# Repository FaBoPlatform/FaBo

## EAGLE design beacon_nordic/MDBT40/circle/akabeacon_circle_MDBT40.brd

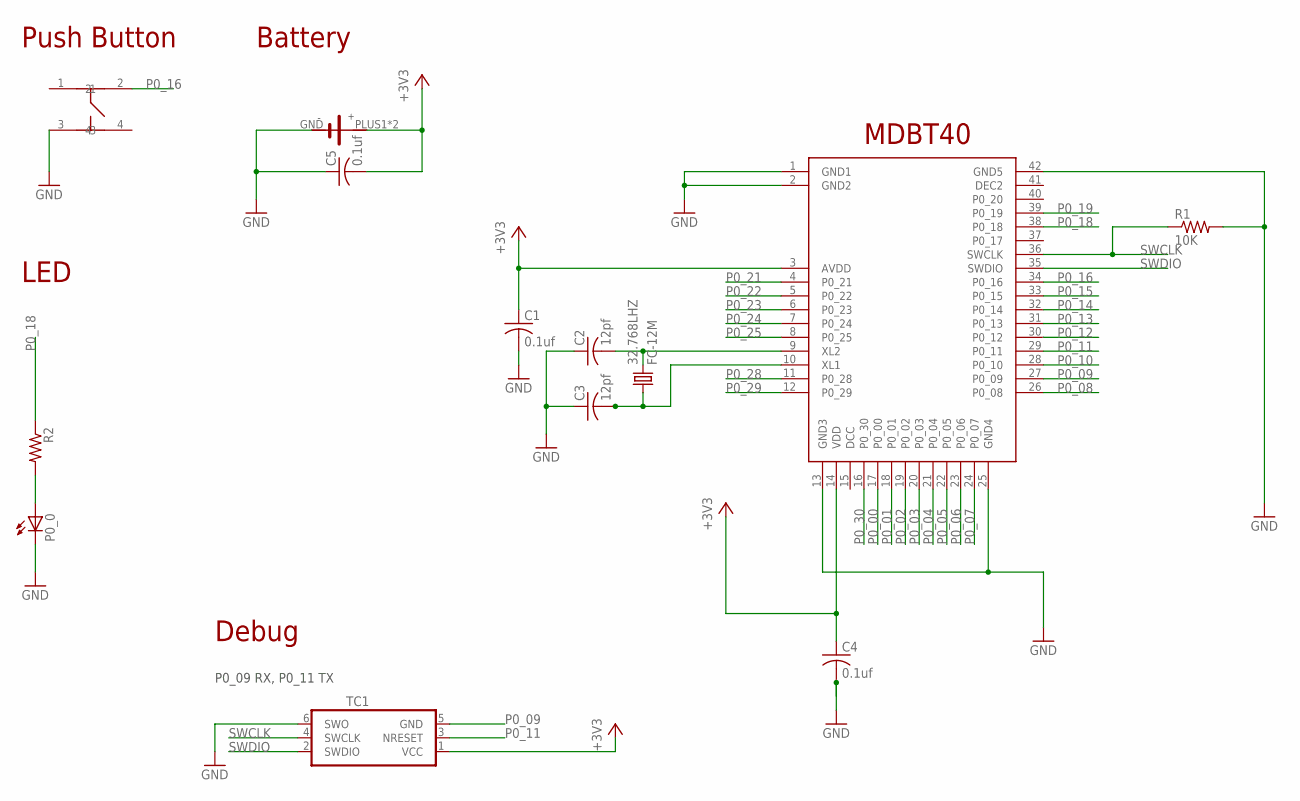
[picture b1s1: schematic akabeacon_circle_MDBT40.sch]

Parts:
32.768LHZ: FC-12M
C1, C4, C5: 0.1uf; C0603
C2, C3: 12pf; C0603
P0_0: LEDCHIP-LED0603; CHIP-LED0603
R1: 10K; R0603
R2: R-US_R0603; R0603
TC1: TC2030-IDC-NL
U$1: RAYTAC-MDBT40
U$5: SWICTH-4P(KMR2); SWITCH-4P(KMR2)
U$7: CIRCLE-TYPE1; CIRCLE-TYE1-TC2030

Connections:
+3V3: C1.1, C4.1, C5.2, TC1.1 (VCC), U$1.3 (AVDD), U$1.14 (VDD), U$7.PLUS1 (VCC), U$7.PLUS2 (VCC)
GND: C1.2, C2.1, C3.1, C4.2, C5.1, P0_0.C, R1.2, TC1.6 (SWO), U$1.1 (GND1), U$1.2 (GND2), U$1.13 (GND3), U$1.25 (GND4), U$1.42 (GND5), U$5.3, U$7.GND
unnamed: P0_0.A, R2.2
unnamed: 32.768LHZ.2, C2.2, U$1.9 (XL2)
unnamed: 32.768LHZ.1, C3.2, U$1.10 (XL1)
P0_00: U$1.17 (P0_00)
P0_01: U$1.18 (P0_01)
P0_02: U$1.19 (P0_02)
P0_03: U$1.20 (P0_03)
P0_04: U$1.21 (P0_04)
P0_05: U$1.22 (P0_05)
P0_06: U$1.23 (P0_06)
P0_07: U$1.24 (P0_07)
P0_08: U$1.26 (P0_08)
P0_09: TC1.5 (GND), U$1.27 (P0_09)
P0_10: U$1.28 (P0_10)
P0_11: TC1.3 (NRESET), U$1.29 (P0_11)
P0_12: U$1.30 (P0_12)
P0_13: U$1.31 (P0_13)
P0_14: U$1.32 (P0_14)
P0_15: U$1.33 (P0_15)
P0_16: U$1.34 (P0_16), U$5.2
P0_18: R2.1, U$1.38 (P0_18)
P0_19: U$1.39 (P0_19)
P0_21: U$1.4 (P0_21)
P0_22: U$1.5 (P0_22)
P0_23: U$1.6 (P0_23)
P0_24: U$1.7 (P0_24)
P0_25: U$1.8 (P0_25)
P0_28: U$1.11 (P0_28)
P0_29: U$1.12 (P0_29)
P0_30: U$1.16 (P0_30)
SWCLK: R1.1, TC1.4 (SWCLK), U$1.36 (SWCLK)
SWDIO: TC1.2 (SWDIO), U$1.35 (SWDIO)

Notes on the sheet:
Battery
Push Button
MDBT40
LED
Debug
P0_09 RX, P0_11 TX

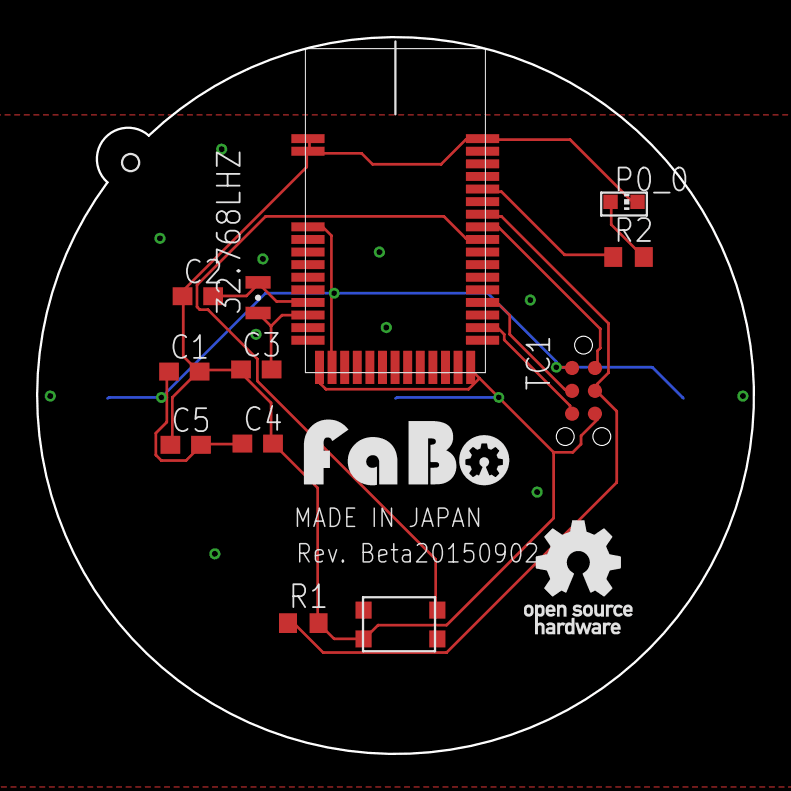
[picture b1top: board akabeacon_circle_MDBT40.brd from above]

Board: 2 copper layers, 39.8 x 39.8 mm, 15 parts (0 on the bottom side), 11 nets.

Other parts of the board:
U$2: LOGO_FABO_M
U$4: LOGO_OSHW_T_M

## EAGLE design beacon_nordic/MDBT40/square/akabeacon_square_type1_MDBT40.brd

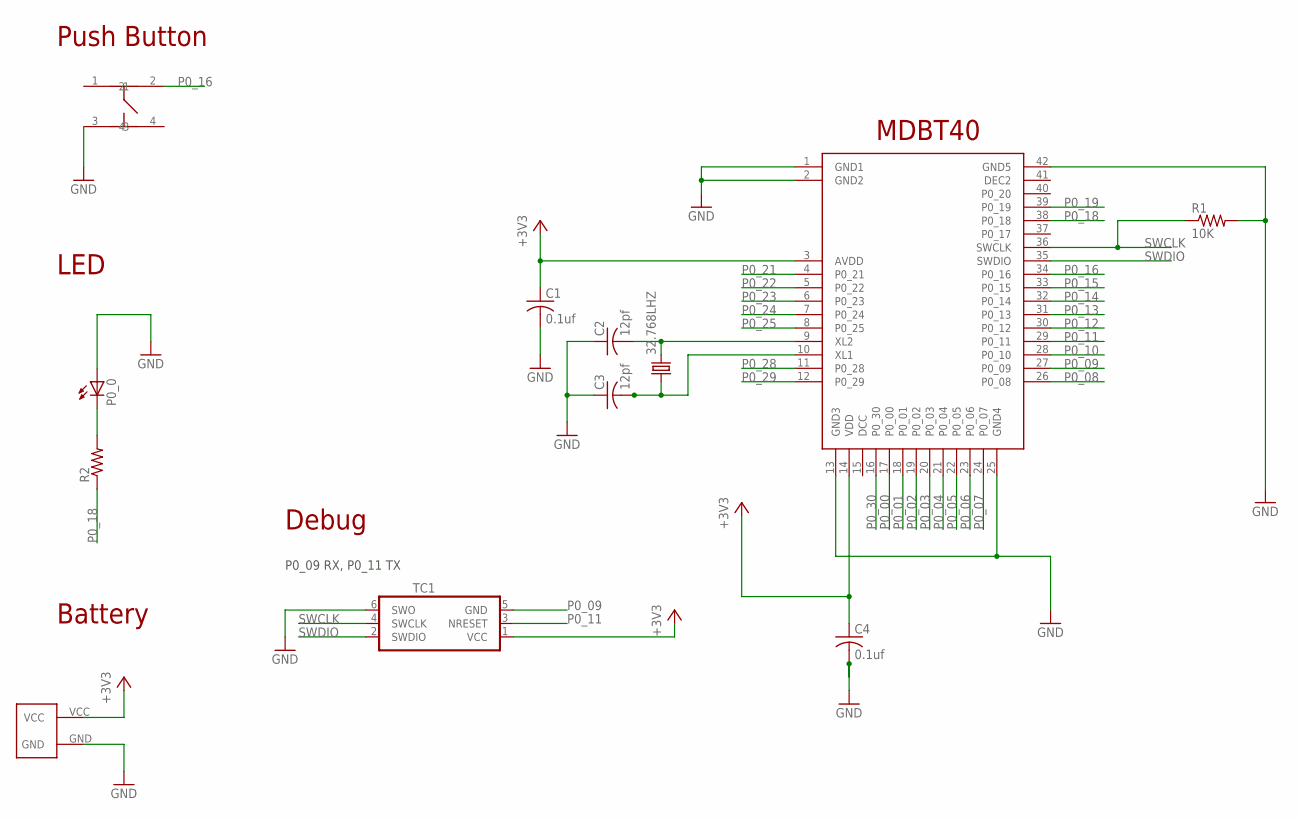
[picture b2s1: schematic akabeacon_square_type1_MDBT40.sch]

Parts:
32.768LHZ: FC-12M
C1, C4: 0.1uf; C0603
C2, C3: 12pf; C0603
P0_0: LEDCHIP-LED0603; CHIP-LED0603
R1: 10K; R0603
R2: R-US_R0603; R0603
TC1: TC2030-IDC-NL
U$2: SQUARE-TYPE1; SQUARE-TYPE1-TC2030
U$3: RAYTAC-MDBT40
U$6: SWICTH-4P(KMR2); SWITCH-4P(KMR2)

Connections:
+3V3: C1.1, C4.1, TC1.1 (VCC), U$2.VCC, U$3.3 (AVDD), U$3.14 (VDD)
GND: C1.2, C2.1, C3.1, C4.2, P0_0.A, R1.2, TC1.6 (SWO), U$2.GND, U$3.1 (GND1), U$3.2 (GND2), U$3.13 (GND3), U$3.25 (GND4), U$3.42 (GND5), U$6.3
LED1: P0_0.C, R2.2
unnamed: 32.768LHZ.2, C2.2, U$3.9 (XL2)
unnamed: 32.768LHZ.1, C3.2, U$3.10 (XL1)
P0_00: U$3.17 (P0_00)
P0_01: U$3.18 (P0_01)
P0_02: U$3.19 (P0_02)
P0_03: U$3.20 (P0_03)
P0_04: U$3.21 (P0_04)
P0_05: U$3.22 (P0_05)
P0_06: U$3.23 (P0_06)
P0_07: U$3.24 (P0_07)
P0_08: U$3.26 (P0_08)
P0_09: TC1.5 (GND), U$3.27 (P0_09)
P0_10: U$3.28 (P0_10)
P0_11: TC1.3 (NRESET), U$3.29 (P0_11)
P0_12: U$3.30 (P0_12)
P0_13: U$3.31 (P0_13)
P0_14: U$3.32 (P0_14)
P0_15: U$3.33 (P0_15)
P0_16: U$3.34 (P0_16), U$6.2
P0_18: R2.1, U$3.38 (P0_18)
P0_19: U$3.39 (P0_19)
P0_21: U$3.4 (P0_21)
P0_22: U$3.5 (P0_22)
P0_23: U$3.6 (P0_23)
P0_24: U$3.7 (P0_24)
P0_25: U$3.8 (P0_25)
P0_28: U$3.11 (P0_28)
P0_29: U$3.12 (P0_29)
P0_30: U$3.16 (P0_30)
SWCLK: R1.1, TC1.4 (SWCLK), U$3.36 (SWCLK)
SWDIO: TC1.2 (SWDIO), U$3.35 (SWDIO)

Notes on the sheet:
Battery
Push Button
Debug
MDBT40
LED
P0_09 RX, P0_11 TX

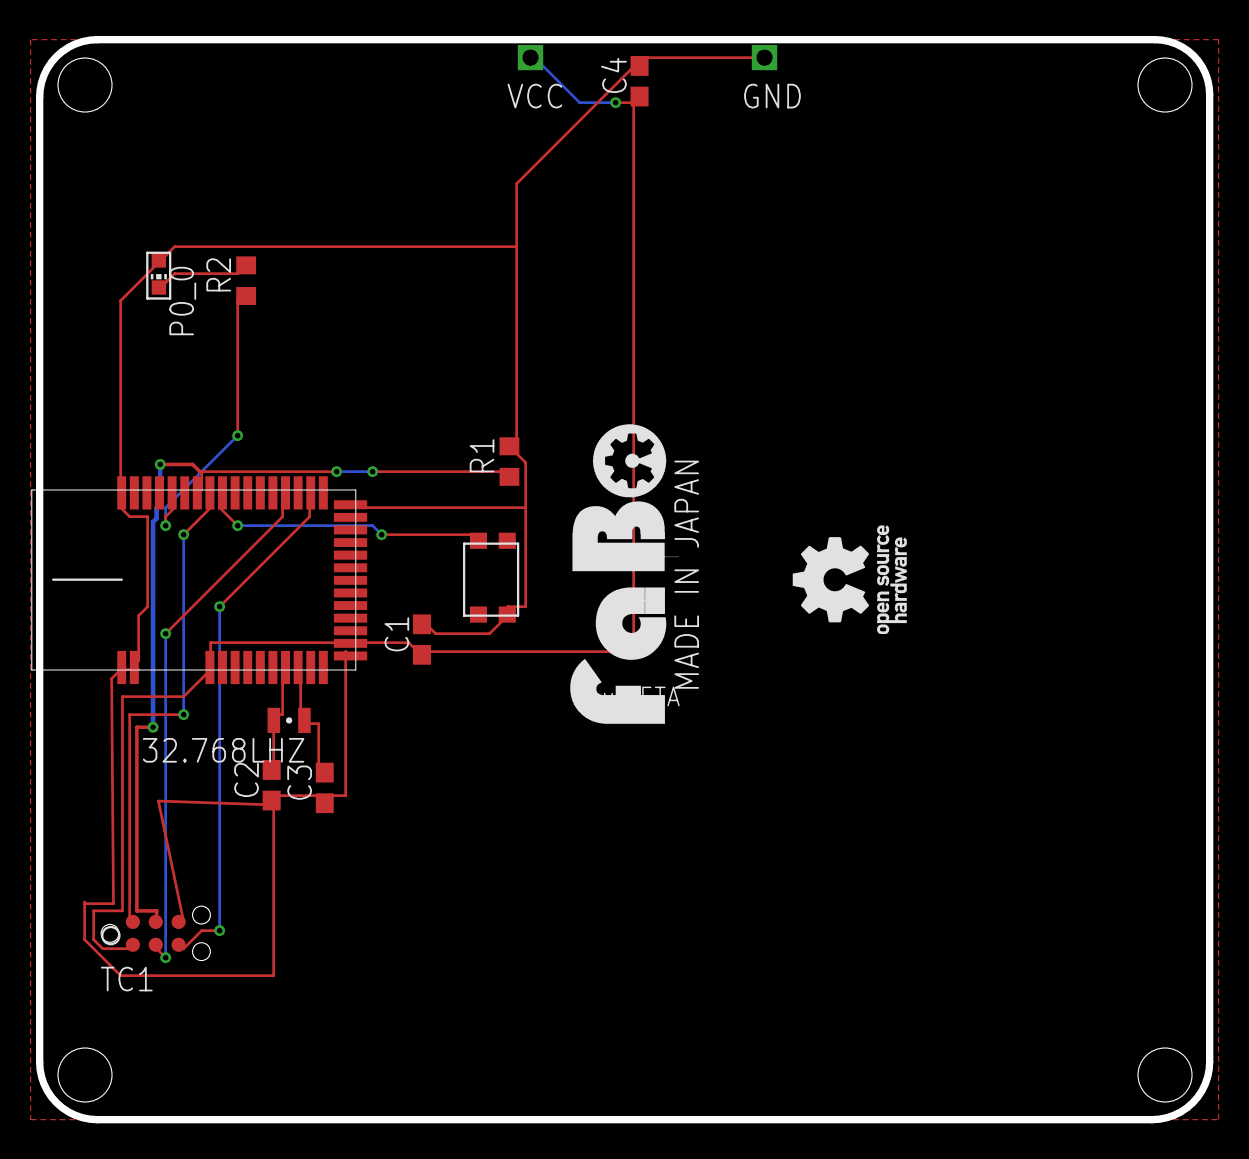
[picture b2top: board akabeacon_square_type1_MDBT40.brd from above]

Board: 2 copper layers, 65.0 x 60.0 mm, 12 parts (0 on the bottom side), 11 nets.

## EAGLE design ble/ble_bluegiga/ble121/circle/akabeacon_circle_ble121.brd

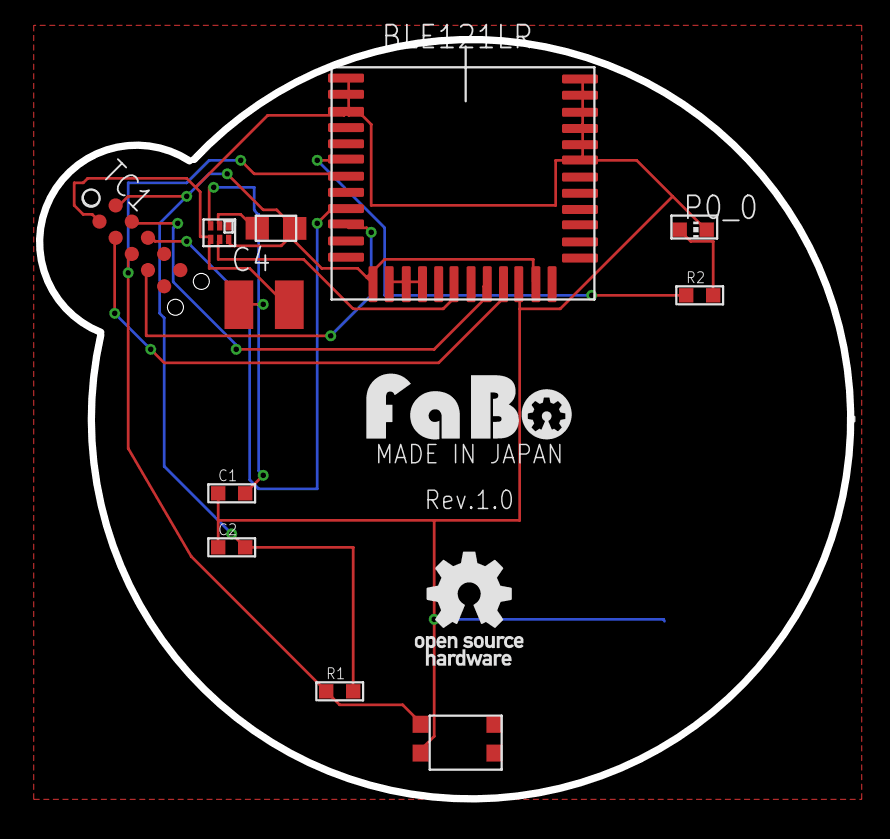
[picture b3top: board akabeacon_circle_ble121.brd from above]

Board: 2 copper layers, 14 parts (0 on the bottom side), 13 nets.

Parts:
BLE1: BLUEGIGA-BLE121LR
C1, C2: 2.2uf; 0603
C4: 100uf; C3225
INDUCTOR1: INDUCTOR-0805
P0_0: CHIP-LED0603
R1: 10k; 0603
R2: 180; 0603
TC1: TC2050-IDC; TC2050-IDC-NL
TPS1: TI-TPS62730
U$1: CIRCLE-TYPE1; CIRCLE-TYE1-TC2030
U$2: LOGO_FABO_M
U$4: LOGO_OSHW_T_M
U$5: SWICTH-4P(KMR2); SWITCH-4P(KMR2)

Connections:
3.3V: BLE1.13, BLE1.23, C2.2, INDUCTOR1.P$2, R1.2, TC1.2, TPS1.6
DEBUG_CLOCK: BLE1.20, TC1.4
DEBUG_DATA: BLE1.21, TC1.3
GND: BLE1.1, BLE1.2, BLE1.3, BLE1.22, BLE1.31, BLE1.32, BLE1.33, BLE1.34, BLE1.35, BLE1.36, C1.1, C2.1, C4.2, P0_0.C, TC1.1, TPS1.4, U$1.GND, U$5.3
unnamed: C1.2, C4.1, TPS1.3, U$1.VCC
unnamed: P0_0.A, R2.2
unnamed: INDUCTOR1.P$1, TPS1.2
unnamed: BLE1.14, BLE1.15, BLE1.16
P0_0: BLE1.6, R2.1
P0_4: BLE1.9, TC1.6
P0_5: BLE1.10, TC1.7
P1_7: BLE1.18, TPS1.5
RESET: BLE1.7, R1.1, TC1.5, U$5.1

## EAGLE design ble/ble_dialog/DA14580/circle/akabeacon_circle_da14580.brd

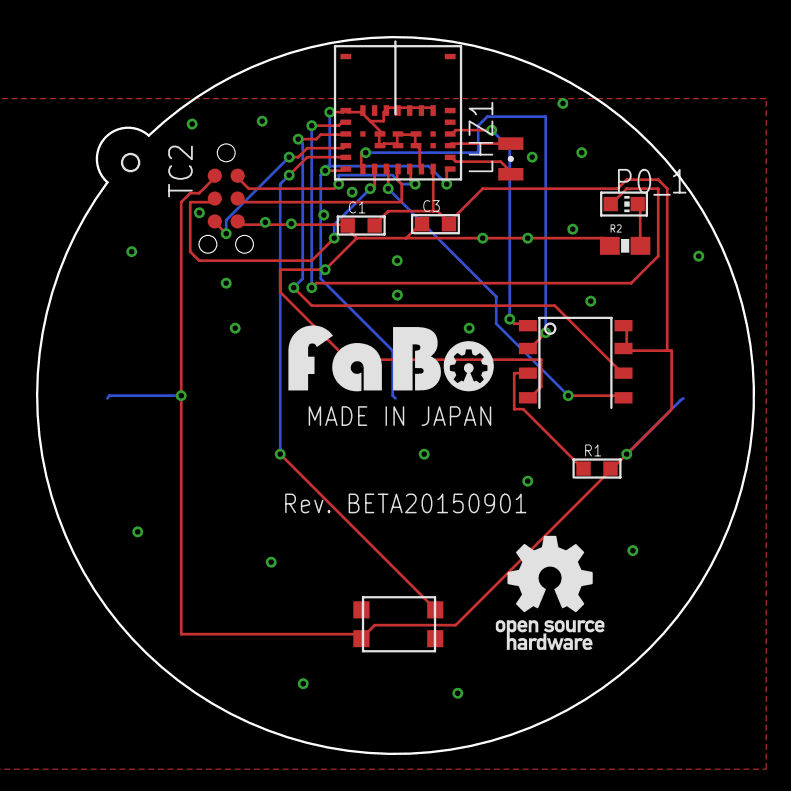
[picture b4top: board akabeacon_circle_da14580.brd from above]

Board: 2 copper layers, 39.8 x 39.8 mm, 13 parts (0 on the bottom side), 16 nets.

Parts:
C1, C3: 2.2uf; 0603
LHZ1: FC-12M
P0_1: CHIP-LED0603
R1: RESISTOR0603; 0603
R2: 180; 0603-RES
TC2: TC2030-IDC-NL
U$1: MURATA-TYPEZY; MURATA_TYPEZY
U$2: LOGO_FABO_M
U$3: CIRCLE-TYPE1; CIRCLE-TYE1-TC2030
U$5: FLASH-MEMORY-2M(WINBOND)
U$6: LOGO_OSHW_T_M
U$7: SWICTH-4P(KMR2); SWITCH-4P(KMR2)

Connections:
+3V3: C1.2, C3.2, R1.2, TC2.1, U$1.7, U$3.PLUS1, U$3.PLUS2, U$5.HOLD#, U$5.VCC, U$7.3
GND: C1.1, C3.1, R2.1, TC2.6, U$1.6, U$1.8, U$1.14, U$1.15, U$1.16, U$1.17, U$1.18, U$1.20, U$1.21, U$1.26, U$1.27, U$1.28, U$1.29, U$1.32, U$1.33, U$1.34, U$3.GND, U$5.GND
LED1: P0_1.C, R2.2
unnamed: R1.1, U$5.WP#
P0_0: U$1.23, U$5.CLK
P0_1: P0_1.A, U$1.22
P0_3: U$1.11, U$5.CS
P0_4: TC2.5, U$1.24
P0_5: U$1.1, U$5.DO
P0_6: U$1.3, U$5.DI
P0_7: TC2.3, U$1.2
RST: U$1.25, U$7.2
SWCLK: TC2.4, U$1.4
SWDIO: TC2.2, U$1.5
XTAL32KM: LHZ1.2, U$1.10
XTAL32KP: LHZ1.1, U$1.9

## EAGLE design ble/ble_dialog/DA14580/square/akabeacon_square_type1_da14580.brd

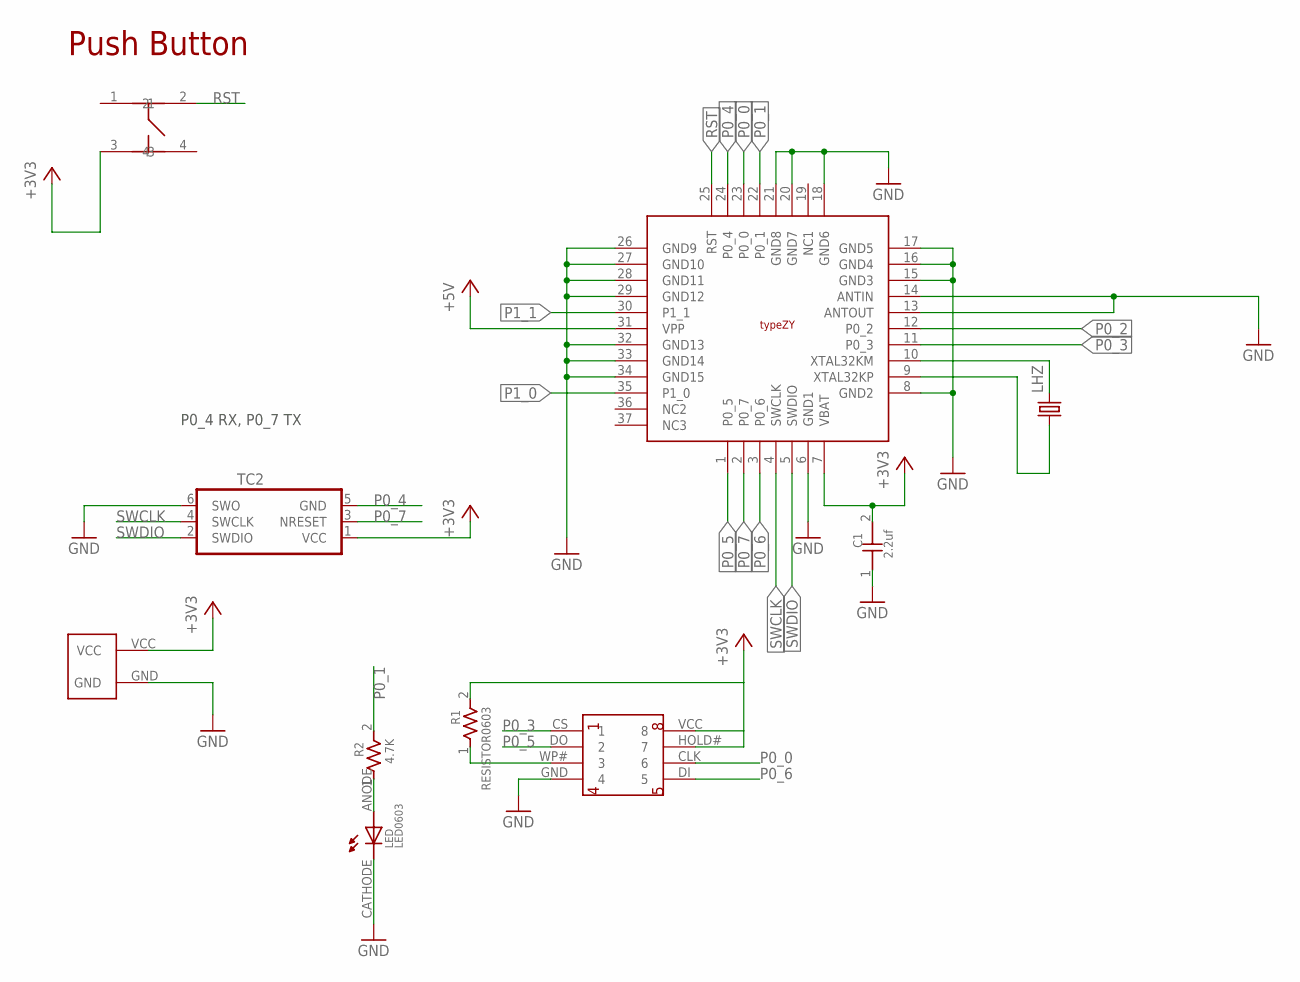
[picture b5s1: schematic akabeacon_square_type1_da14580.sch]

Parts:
C1: 2.2uf; 0603
LED: LED0603; 0603
LHZ: FC-12M
R1: RESISTOR0603; 0603
R2: 4.7K; 0603
TC2: TC2030-IDC-NL
U$2: SQUARE-TYPE1; SQUARE-TYPE1-TC2030
U$3: FLASH-MEMORY-2M(WINBOND)
U$7: SWICTH-4P(KMR2); SWITCH-4P(KMR2)
U$9: MURATA-TYPEZY; MURATA_TYPEZY

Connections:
+3V3: C1.2, R1.2, TC2.1 (VCC), U$2.VCC, U$3.HOLD# (7), U$3.VCC (8), U$7.3, U$9.7 (VBAT)
+5V: U$9.31 (VPP)
GND: C1.1, LED.CATHODE, TC2.6 (SWO), U$2.GND, U$3.GND (4), U$9.6 (GND1), U$9.8 (GND2), U$9.13 (ANTOUT), U$9.14 (ANTIN), U$9.15 (GND3), U$9.16 (GND4), U$9.17 (GND5), U$9.18 (GND6), U$9.20 (GND7), U$9.21 (GND8), U$9.26 (GND9), U$9.27 (GND10), U$9.28 (GND11), U$9.29 (GND12), U$9.32 (GND13), U$9.33 (GND14), U$9.34 (GND15)
unnamed: R1.1, U$3.WP# (3)
unnamed: LED.ANODE, R2.1
P0_0: U$3.CLK (6), U$9.23 (P0_0)
P0_1: R2.2, U$9.22 (P0_1)
P0_2: U$9.12 (P0_2)
P0_3: U$3.CS (1), U$9.11 (P0_3)
P0_4: TC2.5 (GND), U$9.24 (P0_4)
P0_5: U$3.DO (2), U$9.1 (P0_5)
P0_6: U$3.DI (5), U$9.3 (P0_6)
P0_7: TC2.3 (NRESET), U$9.2 (P0_7)
P1_0: U$9.35 (P1_0)
P1_1: U$9.30 (P1_1)
RST: U$7.2, U$9.25 (RST)
SWCLK: TC2.4 (SWCLK), U$9.4 (SWCLK)
SWDIO: TC2.2 (SWDIO), U$9.5 (SWDIO)
XTAL32KM: LHZ.2, U$9.10 (XTAL32KM)
XTAL32KP: LHZ.1, U$9.9 (XTAL32KP)

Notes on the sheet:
Push Button
P0_4 RX, P0_7 TX

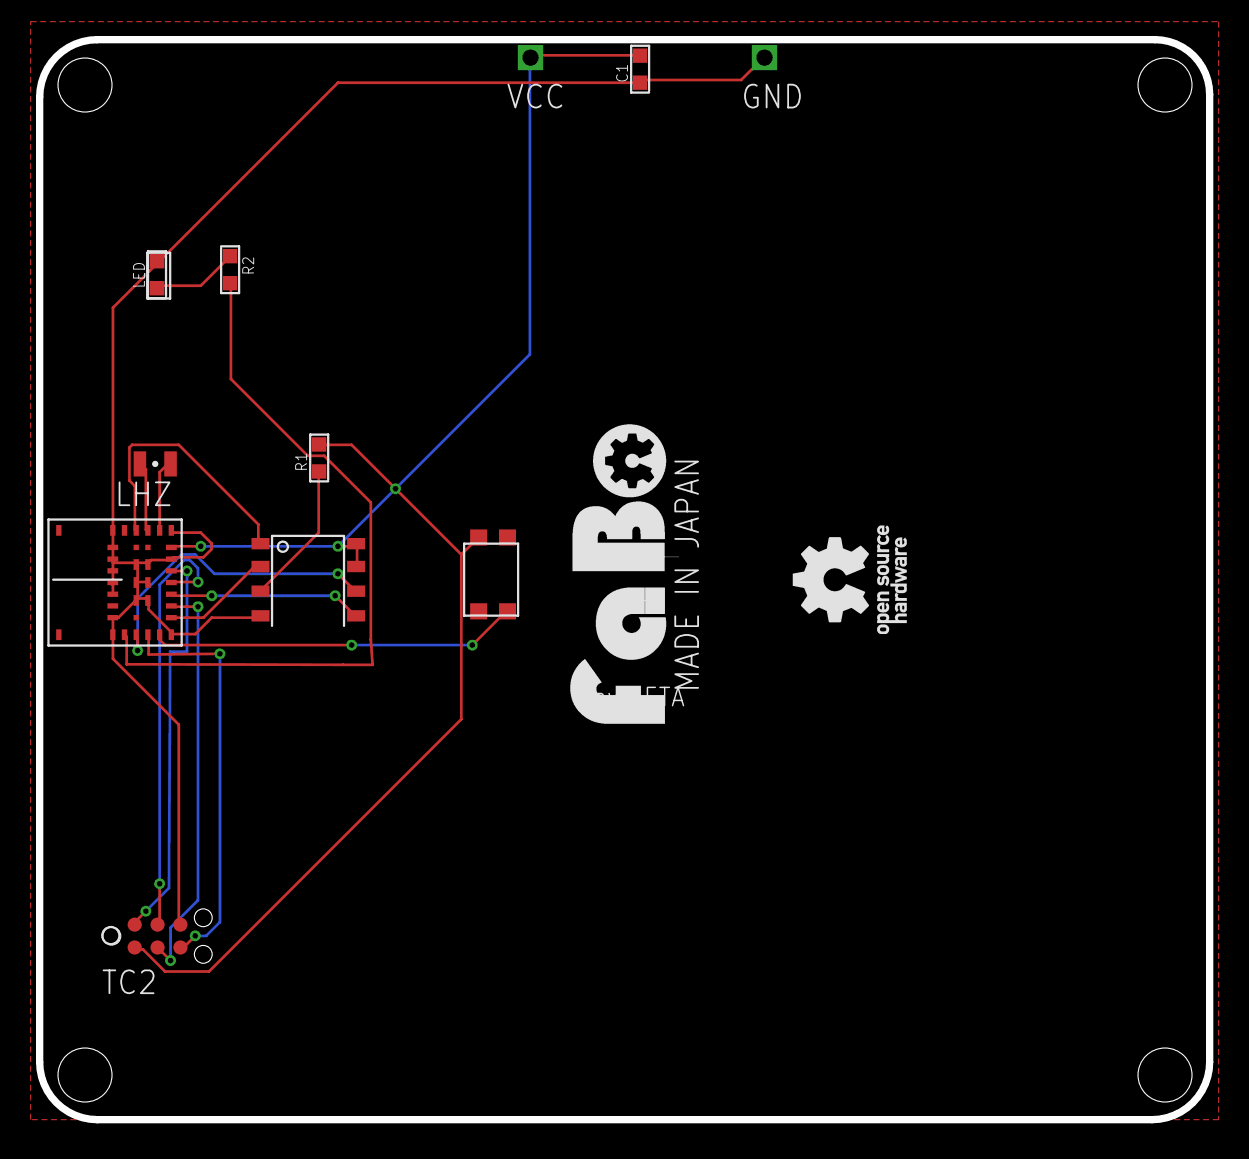
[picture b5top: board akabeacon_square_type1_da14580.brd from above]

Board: 2 copper layers, 65.0 x 60.0 mm, 10 parts (0 on the bottom side), 16 nets.

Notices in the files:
parts and their libraries:
gclue: Released under the Creative Commons
gclue: https://creativecommons.org/licenses/by-sa/4.0
SparkFun: Licensing: CC v3.0 Share-Alike You are welcome to use this library for commercial purposes.
